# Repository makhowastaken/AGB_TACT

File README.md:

# AGB_TACT v2

Tact switch mod for the Game Boy Advance (clicky buttons like the GBA SP but for
regular GBA).

The goal behind this mod is to allow AGB consoles to be repaired (or just
converted) from regular membrane buttons over to the tact switches that GBA SP
consoles use.

Contact pads are designed to accomodate a wide variety of buttons.

## Ordering boards

I've uploaded both boards to OSHPark: [DPad](https://oshpark.com/shared_projects/HXDz5vQI),
[A and B](https://oshpark.com/shared_projects/JWpZMYHv). Best to order them as
flex PCBs to have them as thin as possible.

Gerbers are available in `gerbers` directory.

## Installation

Soldering PCBs to GBA main board is pretty straightforward: line up holes with
corresponding test pads and solder them down.

When soldering buttons, try to center them as best as you can. On DPad this can
make big difference in how they will feel during use.

Next steps depend on the height of the buttons you're using.

### ~0.6mm buttons

For example, ALPS SKRRAAE010 sourced from
[mouser](https://www.mouser.com/ProductDetail/ALPS/SKRRAAE010/?qs=m0BA540hBPeKhAe3239t1w==)
or [lcsc](https://lcsc.com/product-detail/Tactile-Switches_ALPS-Electric-SKRRAAE010_C97437.html).

Depending on circumstances, you might need to add small cardboard pieces onto
each conductive pad on the membranes (pads on aftermarket membranes can be quite
soft and spongy, which doesn't feel great when you're trying to press a tactile
switch). You will probably also need to add cardboard pieces in the middle of
DPad board in order to lift the DPad a bit and prevent it from pressing too many
buttons at once. See the [video](https://youtu.be/q93zTNmFXSk) for more details.

A better option is to 3D print the adapter. Print slow and with supports and snap
the adapter into the DPAD. Install with no membrane. Shimming the middle support
post of the DPAD may be necessary to prevent hitting all four buttons simultaneously.
Too low and you will hit all buttons at the same time, too high and you will not 
be able to hit any buttons. 

### ~1.5mm buttons

I've tried the following buttons, in the order of preference:

* ALPSALPINE SKQGABE010 - ~160gf, 0.25mm travel, 500k cycles ([lcsc](https://lcsc.com/product-detail/Tactile-Switches_ALPSALPINE-SKQGABE010_C115351.html))
* XKB Connectivity TS-1187A-B-B-B - 160gf, 0.2mm travel ([lcsc](https://lcsc.com/product-detail/Tactile-Switches_XKB-Connectivity-TS-1187A-B-B-B_C528026.html))
    * Quite a bit louder than the above
* Diptronics TBEG-W-Q-T/R - 200gf, 0.12mm travel, 200k cycles ([lcsc](https://lcsc.com/product-detail/Tactile-Switches_Diptronics-TBEG-W-Q-T-R_C495931.html))
    * Too fiddly to solder
* XKB Connectivity TS-1187A-C-A-B - 260gf, 0.2mm travel ([lcsc](https://lcsc.com/product-detail/Tactile-Switches_XKB-Connectivity-TS-1187A-C-A-B_C480267.html))
    * Turned out to be a bit too stiff

To make them work you'll need to trim about 1mm from the rubber membranes. On
the aftermarket membranes I have, that amounted to just gently cutting off
conductive pads with a knife, flush to the rest of the membrane.

Additionally, you'll need to stick something about 0.6mm thick in the middle of
DPad PCB in order to prevent DPad from activating too many buttons at once.
Adhesive pad that came with the IPS display worked pretty well in my case.

## Changes in v2.1

* Test pad holes drill diameter reduced to 1mm
* All test pads now have cutouts for easier soldering
* TP6 pad changed to remove overlap with nearby RESET pad on the main board
* GND pad on DPad board moved a bit to the left, reducing the distance to shoulder button

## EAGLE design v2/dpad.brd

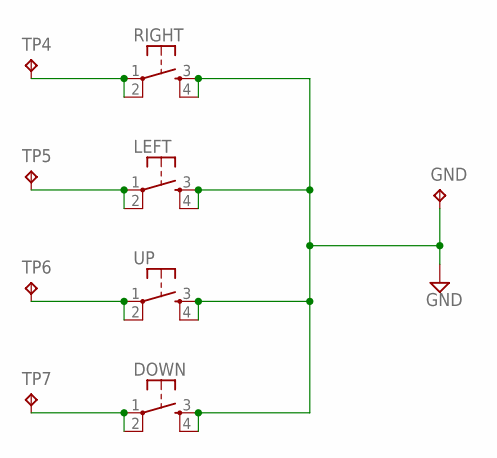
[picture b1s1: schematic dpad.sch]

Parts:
DOWN: BUTTON; SMD_BUTTON
GND: TPPAD1-13; P1-13
LEFT: BUTTON; SMD_BUTTON
RIGHT: BUTTON; SMD_BUTTON
TP4, TP5, TP6, TP7: TESTPAD
UP: BUTTON; SMD_BUTTON

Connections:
GND: DOWN.3 (S), DOWN.4 (S1), GND.TP, LEFT.3 (S), LEFT.4 (S1), RIGHT.3 (S), RIGHT.4 (S1), UP.3 (S), UP.4 (S1)
unnamed: TP6.P$1, UP.1, UP.2 (P1)
unnamed: LEFT.1, LEFT.2 (P1), TP5.P$1
unnamed: RIGHT.1, RIGHT.2 (P1), TP4.P$1
unnamed: DOWN.1, DOWN.2 (P1), TP7.P$1

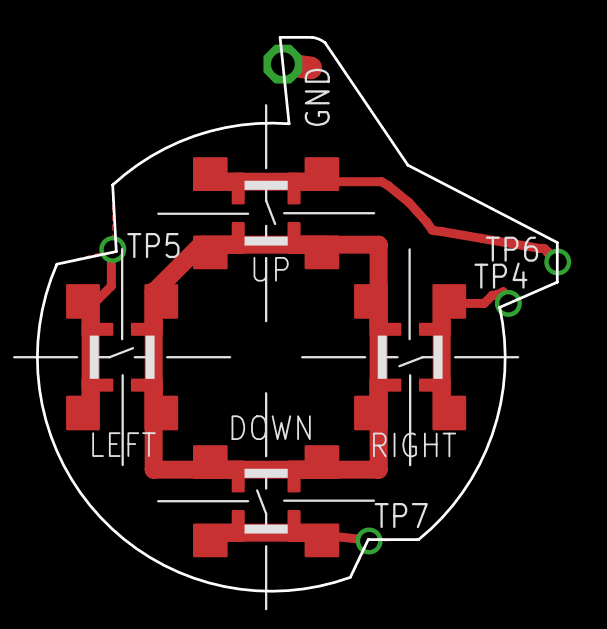
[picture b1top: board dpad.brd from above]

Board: 2 copper layers, 28.9 x 30.8 mm, 9 parts (0 on the bottom side), 5 nets.

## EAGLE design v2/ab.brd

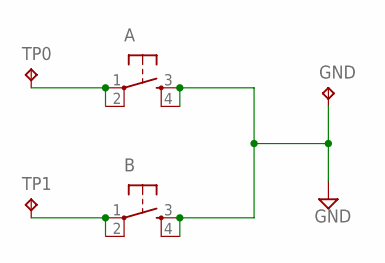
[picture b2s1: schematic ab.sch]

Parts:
A: BUTTON; SMD_BUTTON
B: BUTTON; SMD_BUTTON
GND: TPPAD1-13; P1-13
TP0, TP1: TESTPAD

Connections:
GND: A.3 (S), A.4 (S1), B.3 (S), B.4 (S1), GND.TP
unnamed: A.1, A.2 (P1), TP0.P$1
unnamed: B.1, B.2 (P1), TP1.P$1

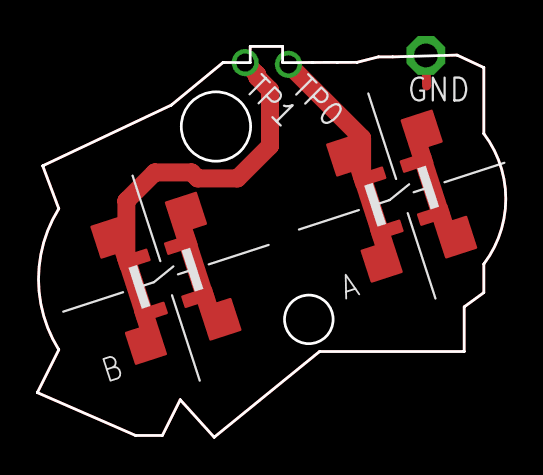
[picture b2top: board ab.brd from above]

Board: 2 copper layers, 26.0 x 21.7 mm, 5 parts (0 on the bottom side), 3 nets.

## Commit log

2020-02-15 Create LICENSE
2020-04-10 Update README.md
    added lcsc link for parts
2021-06-30 Add v2.0
2022-01-18 Update README.md
    added 3D printable dpad adapter and updated description to reflect install options
